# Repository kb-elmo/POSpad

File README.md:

# POSpad

[![CC BY-NC-SA 4.0][cc-by-nc-sa-shield]][cc-by-nc-sa]

### 4-key / POS macropad

---

[STEP files for the case](case/)

[KiCAD PCB files](pcb/)

[Gerbers for PCB production](pcb/gerbers/)

[JLCPCB BOM](pcb/fab/pos_bom_jlc.csv)

[JLCPCB CPL](pcb/fab/pos_cpl_jlc.csv)

[Vial-QMK firmware](firmware/)

---

This work is licensed under a
[Creative Commons Attribution-NonCommercial-ShareAlike 4.0 International License][cc-by-nc-sa].

[![CC BY-NC-SA 4.0][cc-by-nc-sa-image]][cc-by-nc-sa]

[cc-by-nc-sa]: http://creativecommons.org/licenses/by-nc-sa/4.0/
[cc-by-nc-sa-image]: https://licensebuttons.net/l/by-nc-sa/4.0/88x31.png
[cc-by-nc-sa-shield]: https://img.shields.io/badge/License-CC%20BY--NC--SA%204.0-lightgrey.svg

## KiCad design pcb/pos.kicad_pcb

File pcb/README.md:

# POSpad PCB

### Features

- In-switch backlight LEDs
- Powered by an Atmega32u2
- Basic ESD and overvoltage protection
- Centered USB type-C port for a detachable cable
- Fully programmable using [QMK](https://qmk.fm) and [Vial](https://get.vial.today)

---

### Preview

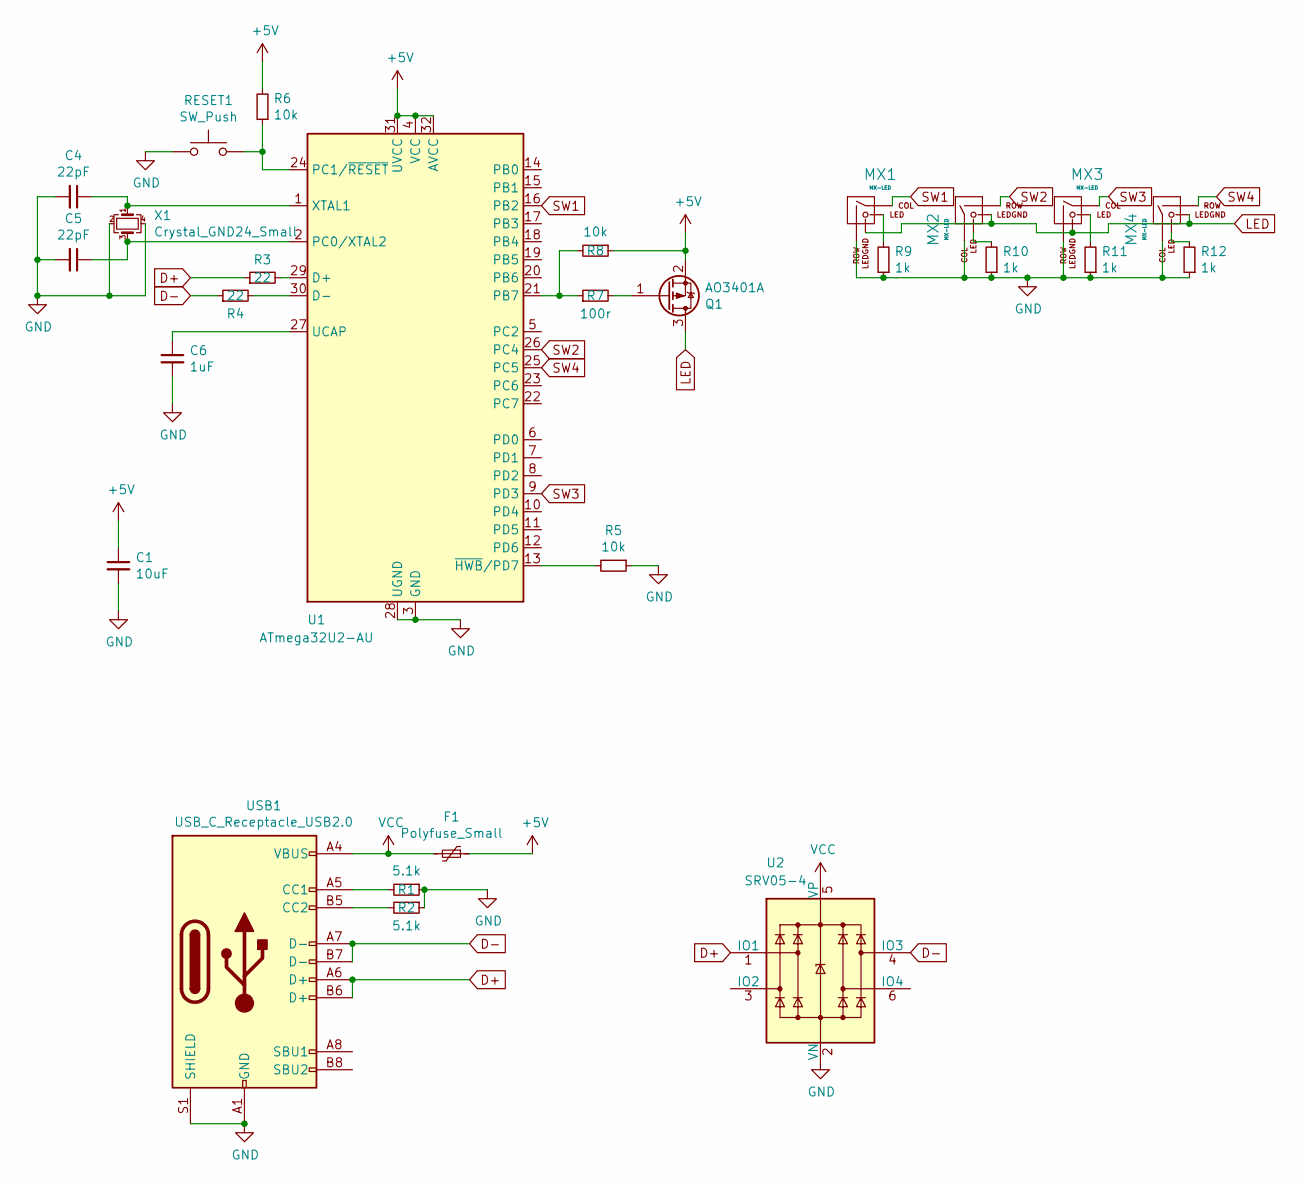
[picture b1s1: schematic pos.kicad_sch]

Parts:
C1: 10uF; C_0603_1608Metric; LCSC C19702
C4, C5: 22pF; C_0603_1608Metric; LCSC C1653
C6: 1uF; C_0603_1608Metric; LCSC C15849
F1: Polyfuse_Small; Fuse_1206_3216Metric; LCSC C69688
MX1, MX2, MX3, MX4: MX-LED; MXOnly-1U
Q1: AO3401A; SOT-23; LCSC C15127
R1, R2: 5.1k; R_0603_1608Metric; LCSC C23186
R3, R4: 22; R_0603_1608Metric; LCSC C23345
R5, R6, R8: 10k; R_0603_1608Metric; LCSC C25804
R7: 100r; R_0603_1608Metric; LCSC C22775
R9, R10, R11, R12: 1k; R_0603_1608Metric; LCSC C21190
RESET1: SW_Push; PinHeader_1x02_P2.00mm_Vertical; LCSC C318884
U1: ATmega32U2-AU; TQFP-32_7x7mm_P0.8mm; LCSC C618733
U2: SRV05-4; SOT-23-6; LCSC C85364
USB1: USB_C_Receptacle_USB2.0; USB_C_Receptacle_HRO_TYPE-C-31-M-12; LCSC C165948
X1: Crystal_GND24_Small; Crystal_SMD_3225-4Pin_3.2x2.5mm; LCSC C13738

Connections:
+5V: C1.1, F1.1, Q1.2 (S), R6.2, R8.1, U1.4 (VCC), U1.31 (UVCC), U1.32 (AVCC)
D+: R3.1, U2.1 (IO1), USB1.A6 (D+), USB1.B6 (D+)
D-: R4.1, U2.4 (IO3), USB1.A7 (D-), USB1.B7 (D-)
GND: C1.2, C4.2, C5.2, C6.2, MX1.2 (ROW), MX2.1 (COL), MX3.2 (ROW), MX4.1 (COL), R1.1, R2.1, R5.1, R9.1, R10.1, R11.1, R12.1, RESET1.1, U1.3 (GND), U1.28 (UGND), U2.2 (VN), USB1.A1 (GND), USB1.A12 (GND), USB1.B1 (GND), USB1.B12 (GND), USB1.S1 (SHIELD), X1.2, X1.4; also elsewhere on the board
LED: MX1.4 (LEDGND), MX2.4 (LEDGND), MX3.4 (LEDGND), MX4.4 (LEDGND), Q1.3 (D)
unnamed: C4.1, U1.1 (XTAL1), X1.1
unnamed: C5.1, U1.2 (PC0/XTAL2), X1.3
unnamed: C6.1, U1.27 (UCAP)
unnamed: MX1.3 (LED), R9.2
unnamed: MX2.3 (LED), R10.2
unnamed: MX3.3 (LED), R11.2
unnamed: MX4.3 (LED), R12.2
unnamed: Q1.1 (G), R7.2
unnamed: R1.2, USB1.A5 (CC1)
unnamed: R2.2, USB1.B5 (CC2)
unnamed: R3.2, U1.29 (D+)
unnamed: R4.2, U1.30 (D-)
unnamed: R5.2, U1.13 (~HWB/PD7)
unnamed 18: R6.1, RESET1.2, U1.24 (PC1/~RESET); also elsewhere on the board
unnamed: R7.1, R8.2, U1.21 (PB7)
SW1: MX1.1 (COL), U1.16 (PB2)
SW2: MX2.2 (ROW), U1.26 (PC4)
SW3: MX3.1 (COL), U1.9 (PD3)
SW4: MX4.2 (ROW), U1.25 (PC5)
VCC: F1.2, U2.5 (VP), USB1.A4 (VBUS), USB1.A9 (VBUS), USB1.B4 (VBUS), USB1.B9 (VBUS)

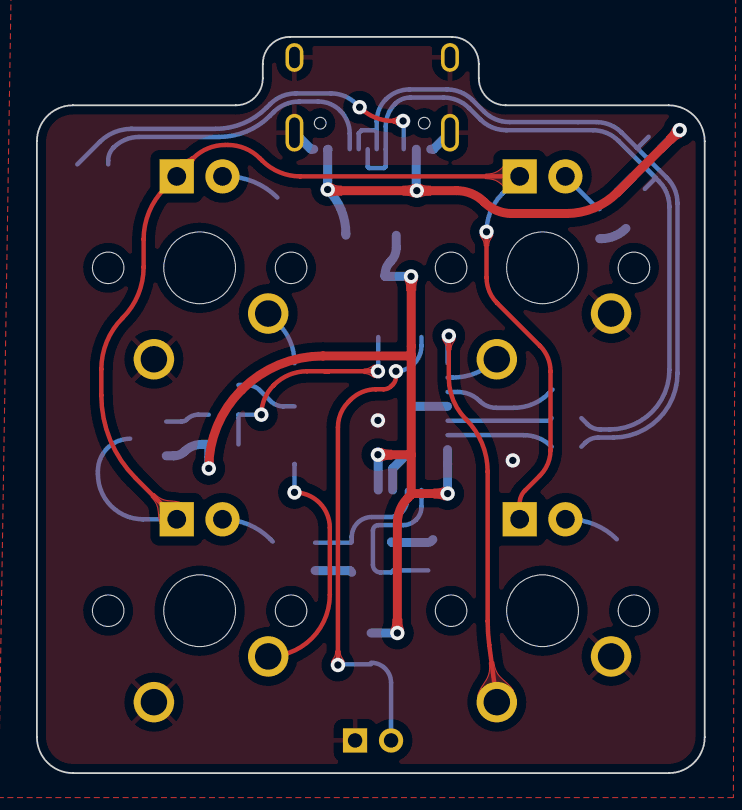
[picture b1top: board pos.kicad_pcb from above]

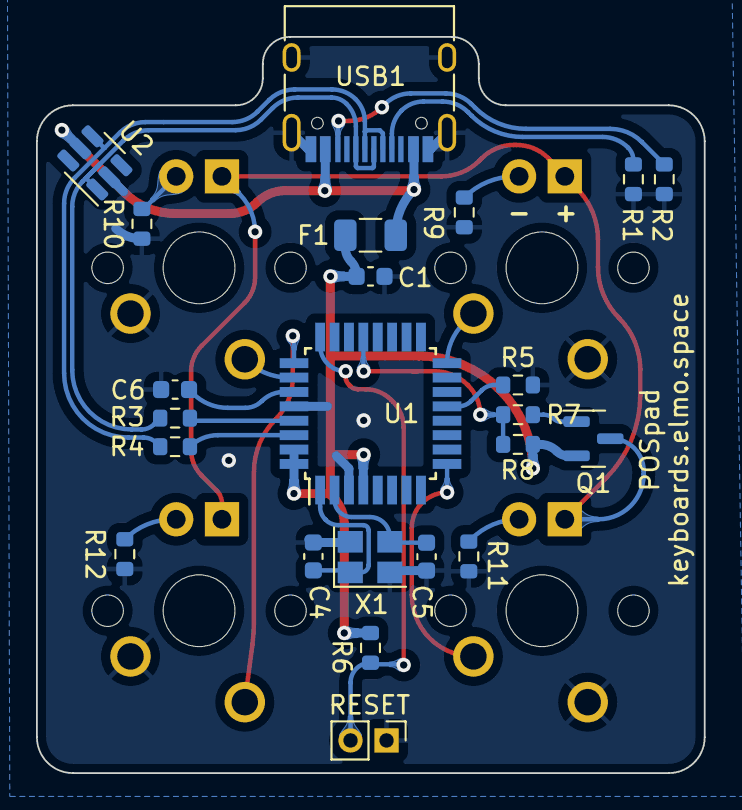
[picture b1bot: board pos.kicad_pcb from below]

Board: 2 copper layers, 37.1 x 40.9 mm, 27 parts (23 on the bottom side), 25 nets.

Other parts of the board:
RESET: SW_Push; PinHeader_1x02_P2.00mm_Vertical

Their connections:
GND: RESET.1; also elsewhere on the board
unnamed 18: RESET.2; also elsewhere on the board

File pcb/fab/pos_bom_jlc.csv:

"Comment","Designator","Footprint","LCSC Part #"
"10uF","C1","C_0603_1608Metric","C19702"
"22pF","C4,C5","C_0603_1608Metric","C1653"
"1uF","C6","C_0603_1608Metric","C15849"
"Polyfuse_Small","F1","Fuse_1206_3216Metric","C69688"
"AO3401A","Q1","SOT-23","C15127"
"5.1k","R1,R2","R_0603_1608Metric","C23186"
"22","R3,R4","R_0603_1608Metric","C23345"
"10k","R5,R6,R8","R_0603_1608Metric","C25804"
"100r","R7","R_0603_1608Metric","C22775"
"1k","R9,R10,R11,R12","R_0603_1608Metric","C21190"
"SW_Push","RESET1","PinHeader_1x02_P2.00mm_Vertical","C318884"
"ATmega32U2-AU","U1","TQFP-32_7x7mm_P0.8mm","C618733"
"SRV05-4","U2","SOT-23-6","C85364"
"USB_C_Receptacle_USB2.0","USB1","USB_C_Receptacle_HRO_TYPE-C-31-M-12","C165948"
"Crystal_GND24_Small","X1","Crystal_SMD_3225-4Pin_3.2x2.5mm","C13738"
